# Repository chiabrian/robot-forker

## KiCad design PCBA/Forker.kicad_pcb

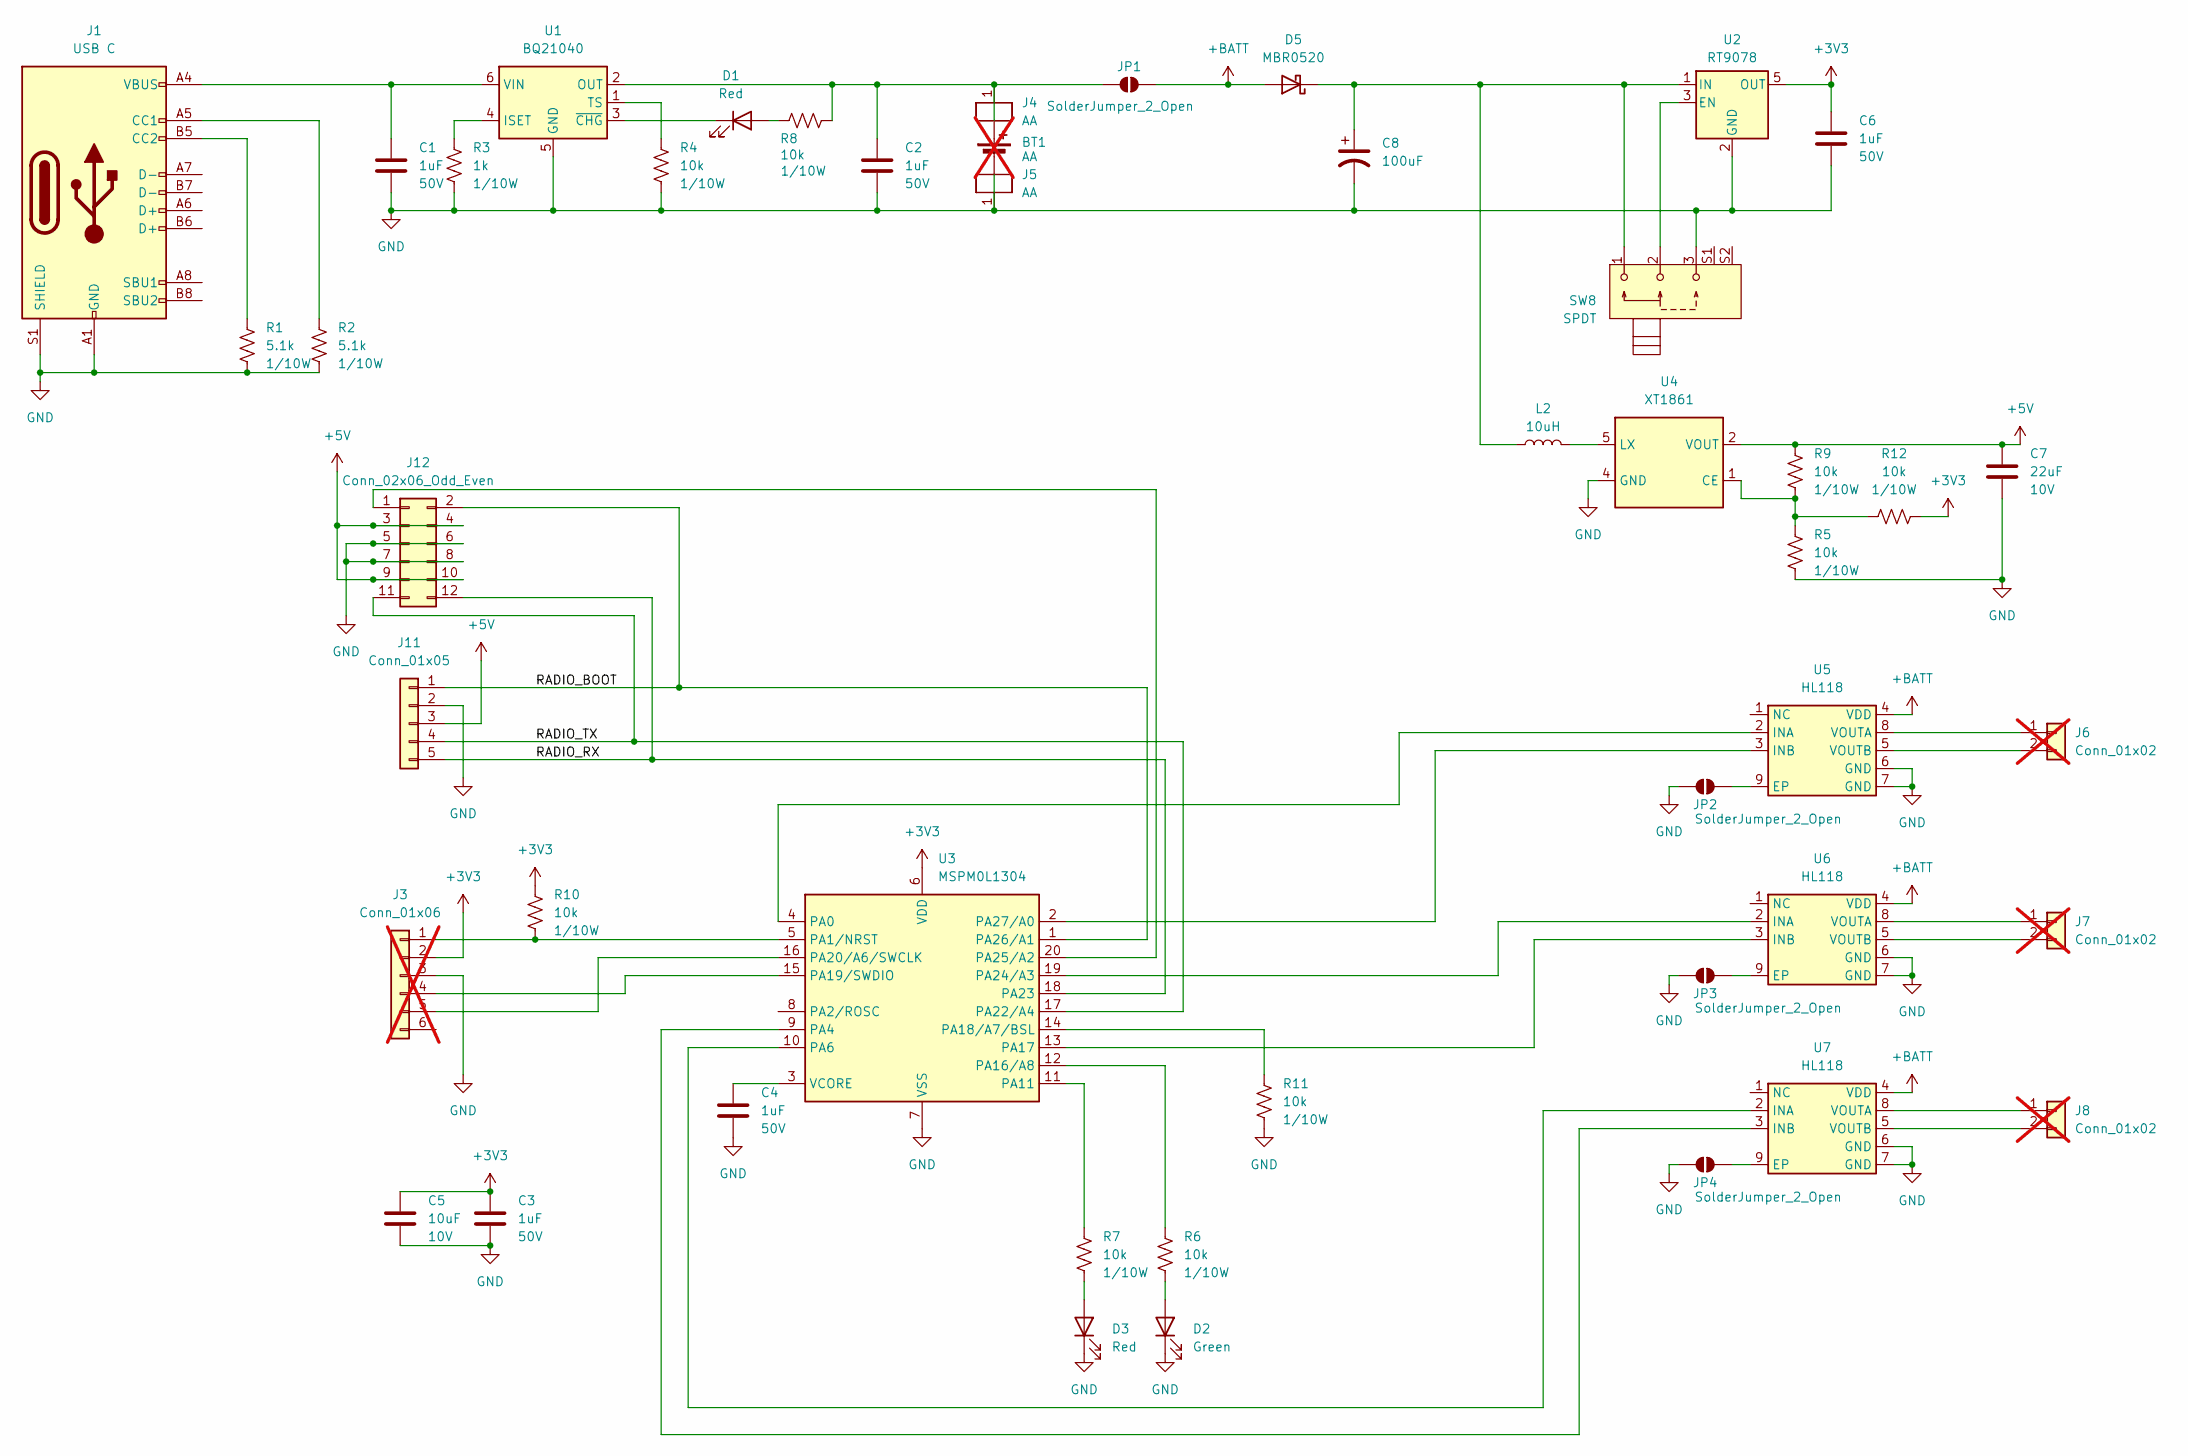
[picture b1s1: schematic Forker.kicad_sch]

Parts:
BT1: AA; Battery_Holder_MPD_BCAAPC; Manufacturer Part Numbe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 2460; LCSC Part Number C5370863; not fitted
C1, C2, C3, C4, C6: 1uF; C_0603_1608Metric; Voltage 50V; Tolerance 10%; Manufacturer Part Numbe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 CL10A105KB8NNNC; LCSC Part Number C15849
C5: 10uF; C_0603_1608Metric; Voltage 10V; Tolerance 10%; Manufacturer Part Numbe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 CL10A106KP8NNNC; LCSC Part Number C19702
C7: 22uF; C_0603_1608Metric; Voltage 10V; Tolerance 20%; Manufacturer Part Numbe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 CL10A226MP8NUNE; LCSC Part Number C86295
C8: 100uF; CP_Radial_D6.3mm_P2.50mm
D1, D3: Red; LED_0603_1608Metric_Pad1.05x0.95mm_HandSolder; Manufacturer Part Numbe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 KT-0603R; LCSC Part Number C2286
D2: Green; LED_0603_1608Metric_Pad1.05x0.95mm_HandSolder; Manufacturer Part Numbe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 KT-0603G; LCSC Part Number C12624
D5: MBR0520; D_SOD-123
J1: USB C; USBC_16P; Voltage 20V; Manufacturer Part Numbe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 HC-TYPE-C-16P-01A; LCSC Part Number C2894897
J3: Conn_01x06; PinHeader_1x06_P2.54mm_Vertical; not fitted
J4, J5: AA; Battery_Clip_Keystone_53; Manufacturer Part Numbe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 53; LCSC Part Number C5352788
J6, J7, J8: Conn_01x02; PinHeader_1x02_P2.54mm_Vertical; not fitted
J11: Conn_01x05; PinHeader_1x05_P2.54mm_Horizontal
J12: Conn_02x06_Odd_Even; PinHeader_2x06_P2.54mm_Horizontal
JP1, JP2, JP3, JP4: SolderJumper_2_Open; SolderJumper-2_P1.3mm_Open_TrianglePad1.0x1.5mm
L2: 10uH; L_4.5x4.0_H3.2; Tolerance 20%; Manufacturer Part Numbe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 CD43-100M; LCSC Part Number C18734467
R1, R2: 5.1k; R_0603_1608Metric_Pad0.98x0.95mm_HandSolder; Tolerance 1%; Manufacturer Part Numbe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 RC0603FR-075K1L; LCSC Part Number C23186
R3: 1k; R_0603_1608Metric_Pad0.98x0.95mm_HandSolder; Tolerance 1%; Manufacturer Part Numbe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 RC0603FR-071KL; LCSC Part Number C21190
R4, R5, R6, R7, R8, R9, R10, R11, R12: 10k; R_0603_1608Metric_Pad0.98x0.95mm_HandSolder; Tolerance 1%; Manufacturer Part Numbe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 RC0603FR-0710KL; LCSC Part Number C25804
SW8: SPDT; SW_SPDT_Slide_CK_SK12D07VG4; Voltage 30V; Manufacturer Part Numbe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 SK12D07VG4; LCSC Part Number C22435621
U1: BQ21040; SOT-23-6; Voltage 3.5-28V; Manufacturer Part Numbe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 BQ21040DBVR; LCSC Part Number C202311
U2: RT9078; SOT-23-5; Voltage 1.2-5.5V; Manufacturer Part Numbe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 RT9078-33GJ5; LCSC Part Number C110427
U3: MSPM0L1304; TI_DGS20; Voltage 1.62-3.6V; Manufacturer Part Numbe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 MSPM0L1304TDGS20R; LCSC Part Number C22362611
U4: XT1861; SOT-23-5; Voltage 1.8-5V; Manufacturer Part Numbe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 XT1861B502SR-G; LCSC Part Number C3008013
U5, U6, U7: HL118; SOP-8-1EP_3.9x4.9mm_P1.27mm_EP2.4x3.3mm; Voltage 1.8-8.5V; Manufacturer Part Numbe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 HL118; LCSC Part Number C42372074

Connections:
+3V3: C3.1, C5.1, C6.1, J3.2, R10.1, R12.2, U2.5 (OUT), U3.6 (VDD)
+5V: C7.1, J11.3, J12.3, J12.4, J12.9, J12.10, R9.1, U4.2 (VOUT)
+BATT: D5.2 (A), JP1.2 (B), U5.4 (VDD), U6.4 (VDD), U7.4 (VDD)
/RADIO_BOOT: J11.1, J12.2, U3.1 (PA26/A1)
/RADIO_RX: J11.5, J12.12, U3.18 (PA23)
/RADIO_TX: J11.4, J12.11, U3.17 (PA22/A4)
GND: BT1.2 (-), C1.2, C2.2, C3.2, C4.2, C5.2, C6.2, C7.2, C8.2, D2.1 (K), D3.1 (K), J1.A1 (GND), J1.A12 (GND), J1.B1 (GND), J1.B12 (GND), J1.S1 (SHIELD), J3.3, J5.1, J11.2, J12.5, J12.6, J12.7, J12.8, JP2.2 (B), JP3.2 (B), JP4.2 (B), R1.2, R2.2, R3.2, R4.1, R5.2, R11.2, SW8.3, U1.5 (GND), U2.2 (GND), U3.7 (VSS), U4.4 (GND), U5.6 (GND), U5.7 (GND), U6.6 (GND), U6.7 (GND), U7.6 (GND), U7.7 (GND)
unnamed: BT1.1 (+), C2.1, J4.1, JP1.1 (A), R8.2, U1.2 (OUT)
unnamed: D1.2 (A), R8.1
unnamed: D1.1 (K), U1.3 (~CHG)
unnamed: D2.2 (A), R6.2
unnamed: D3.2 (A), R7.2
unnamed: C8.1, D5.1 (K), L2.1, SW8.1, U2.1 (IN)
unnamed: J1.A5 (CC1), R2.1
unnamed: J1.B5 (CC2), R1.1
unnamed: J3.1, R10.2, U3.5 (PA1/NRST)
unnamed: J3.4, U3.15 (PA19/SWDIO)
unnamed: J3.5, U3.16 (PA20/A6/SWCLK)
unnamed: J6.1, U5.8 (VOUTA)
unnamed: J6.2, U5.5 (VOUTB)
unnamed: J7.1, U6.8 (VOUTA)
unnamed: J7.2, U6.5 (VOUTB)
unnamed: J8.1, U7.8 (VOUTA)
unnamed: J8.2, U7.5 (VOUTB)
unnamed: J12.1, U3.20 (PA25/A2)
unnamed: JP2.1 (A), U5.9 (EP)
unnamed: JP3.1 (A), U6.9 (EP)
unnamed: JP4.1 (A), U7.9 (EP)
unnamed: R3.1, U1.4 (ISET)
unnamed: R4.2, U1.1 (TS)
unnamed: C1.1, J1.A4 (VBUS), J1.A9 (VBUS), J1.B4 (VBUS), J1.B9 (VBUS), U1.6 (VIN)
unnamed: SW8.2, U2.3 (EN)
unnamed: U3.4 (PA0), U5.2 (INA)
unnamed: U3.9 (PA4), U7.3 (INB)
unnamed: U3.10 (PA6), U7.2 (INA)
unnamed: R7.1, U3.11 (PA11)
unnamed: R6.1, U3.12 (PA16/A8)
unnamed: U3.13 (PA17), U6.3 (INB)
unnamed: R11.1, U3.14 (PA18/A7/BSL)
unnamed: U3.19 (PA24/A3), U6.2 (INA)
unnamed: U3.2 (PA27/A0), U5.3 (INB)
unnamed: C4.1, U3.3 (VCORE)
unnamed: R5.1, R9.2, R12.1, U4.1 (CE)
unnamed: L2.2, U4.5 (LX)

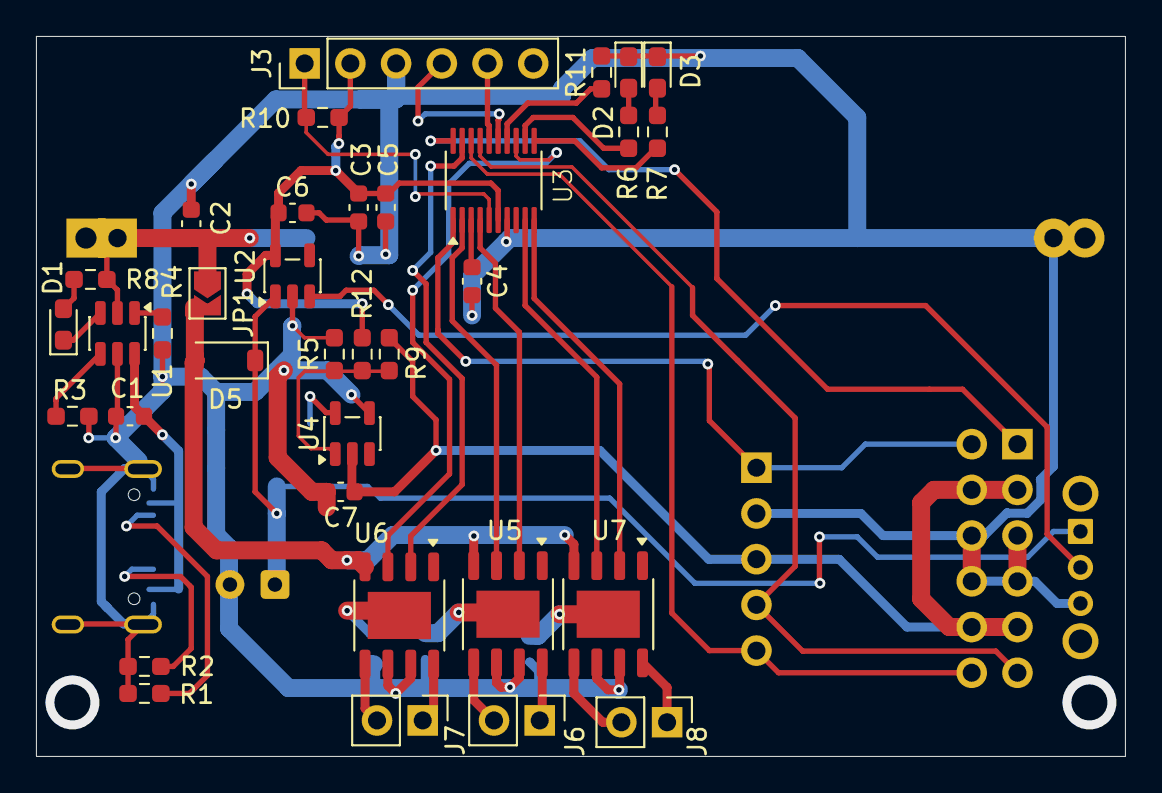
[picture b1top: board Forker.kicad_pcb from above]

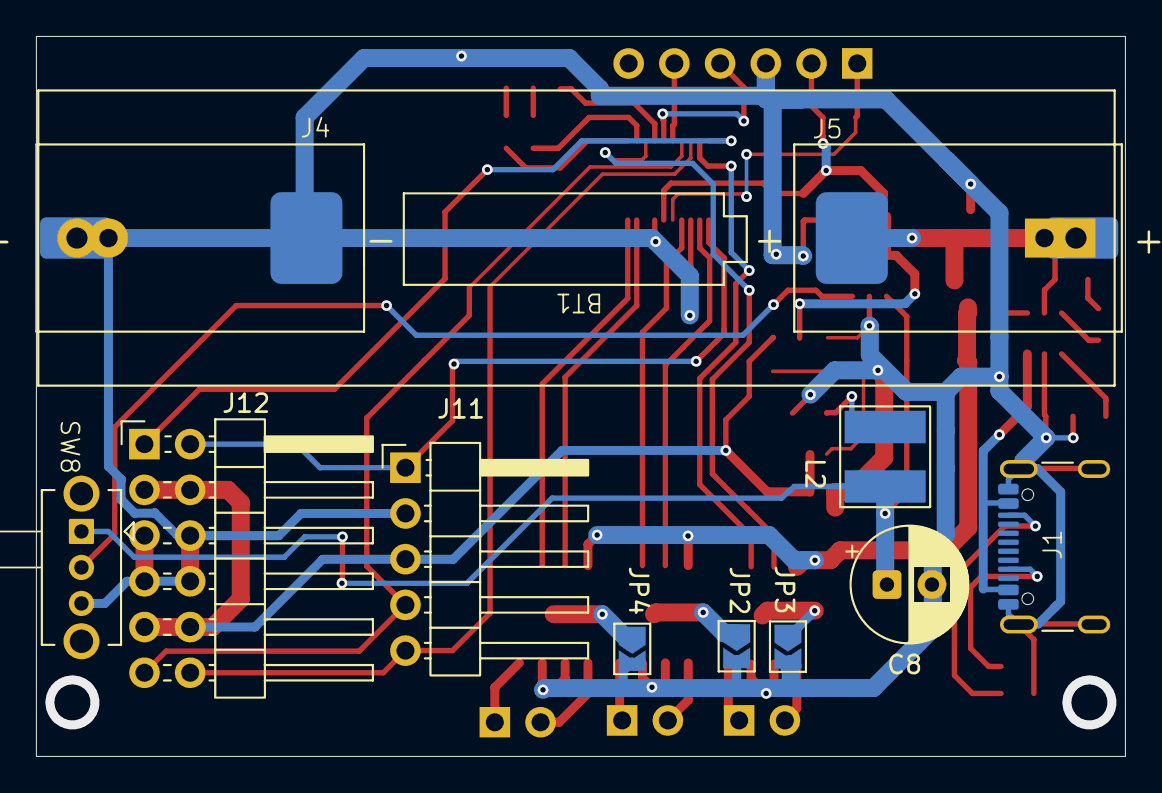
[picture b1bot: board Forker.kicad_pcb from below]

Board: 2 copper layers, 60.5 x 40.0 mm, 47 parts (12 on the bottom side), 44 nets.

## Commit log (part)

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2026-03-15 Update Base
2026-03-22 Add Flat motor
2026-04-19 Latest Commit
2026-04-19 Update Weapon Arm
2026-04-20 Add Cover
2026-04-26 -Add PCBA
2026-04-27 Update PCB Layout
2026-04-30 -Update PCBA connector location -Add cutouts for PCBA -Add Mounting Holes
2026-05-03 Add Full Body Spinner Add 25mm ID 3mm Oring
2026-05-25 Add Firmware
2026-05-29 -Update Pinout for PWM -Add Mixing Algorithm for PWM
